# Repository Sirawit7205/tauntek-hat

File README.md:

# Tauntek LogIC Tester Hat

A controller hat for Tauntek LogIC Tester that eliminated a need for external terminal and power source.

The hat features a 3.5" TFT Display, a rotary encoder, and a USB PD circuit to provide tester with 9V directly from USB Type-C.

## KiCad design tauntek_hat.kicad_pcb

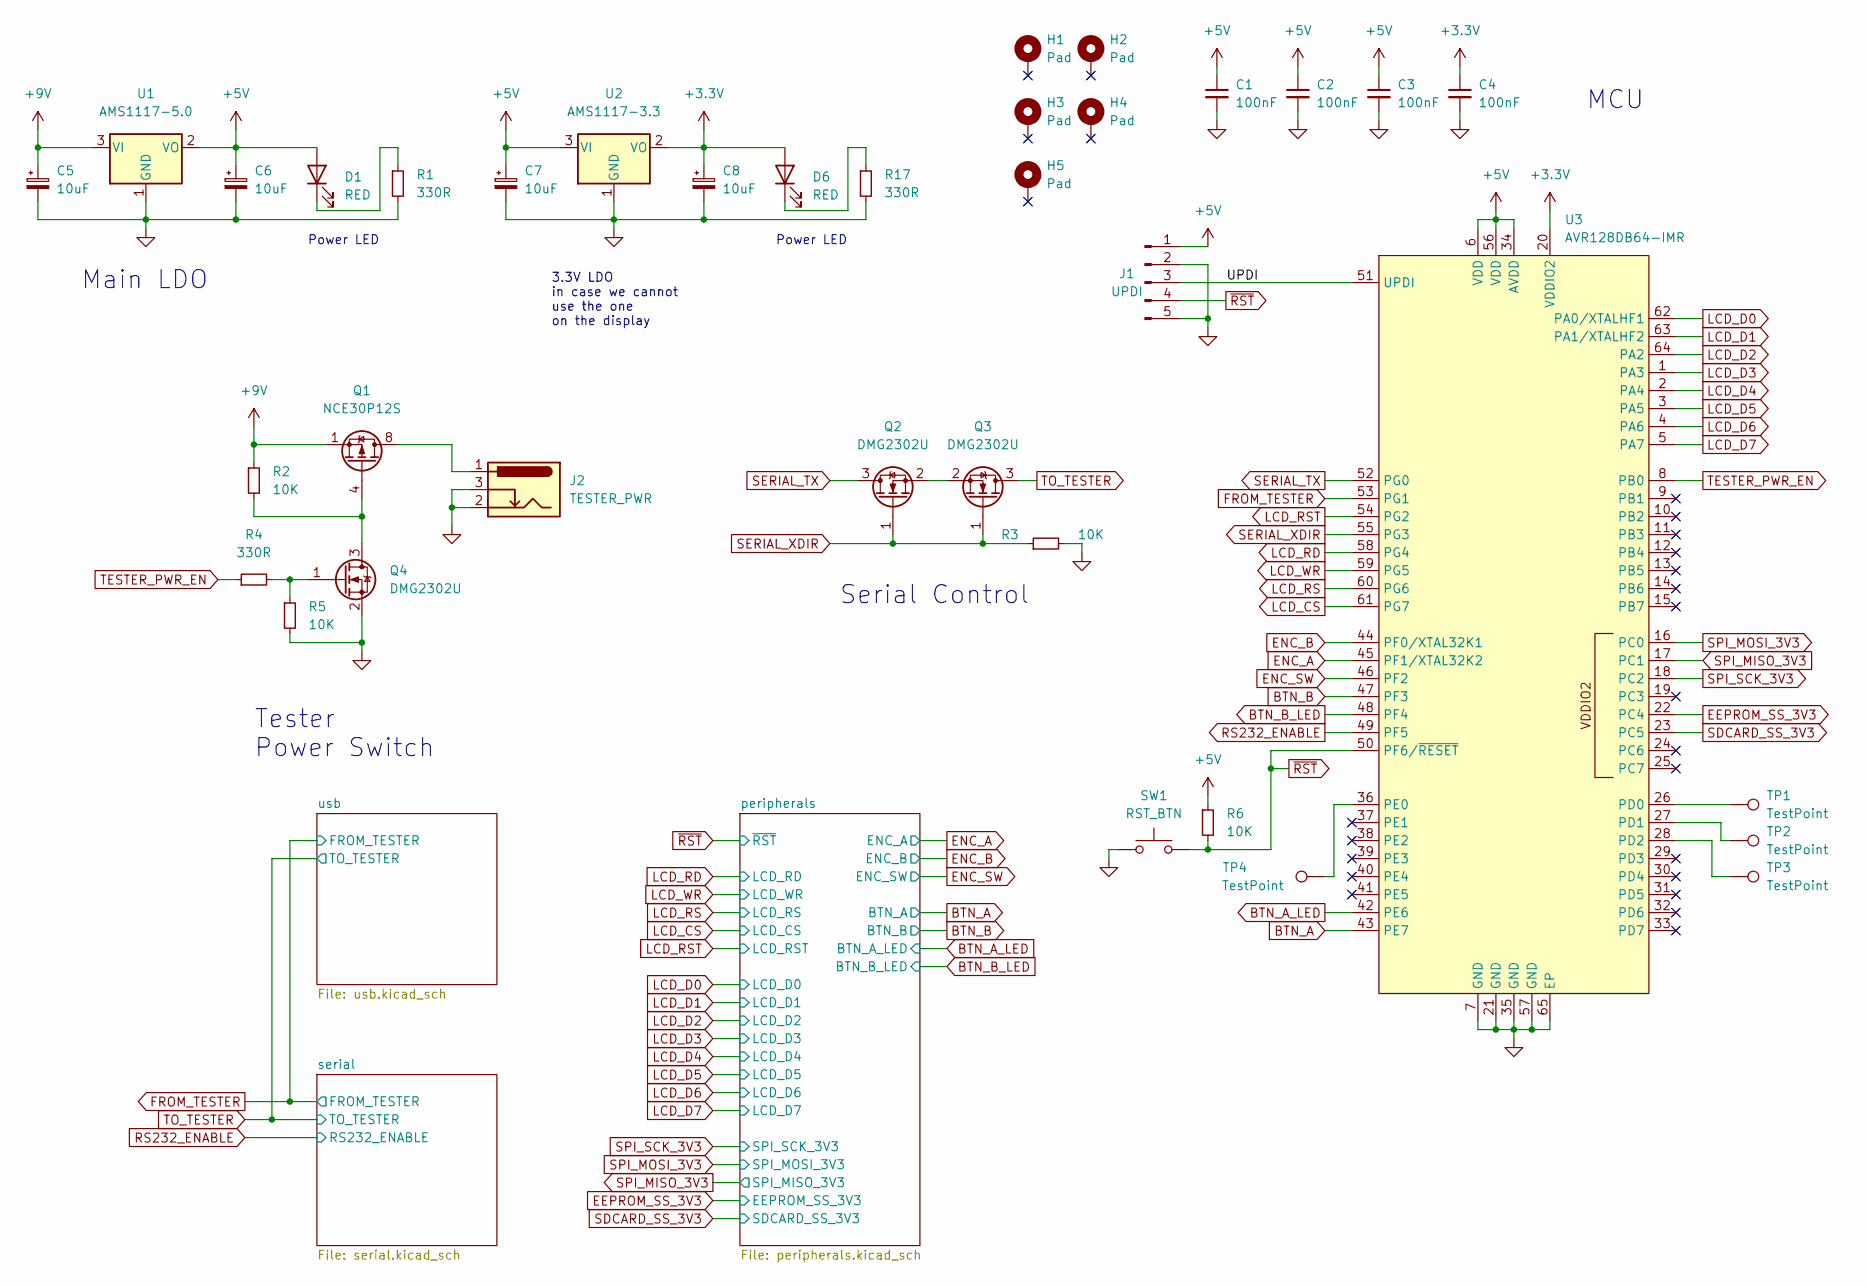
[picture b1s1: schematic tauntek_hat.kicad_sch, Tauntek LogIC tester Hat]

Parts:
C1, C2, C3, C4: 100nF; C_0603_1608Metric
C5, C6, C7, C8: 10uF; CP_Radial_D5.0mm_P2.00mm
D1, D6: RED; LED_D3.0mm
H1, H2, H3, H4, H5: Pad; MountingHole_3mm_Pad
J1: UPDI; PinHeader_1x05_P2.54mm_Vertical
J2: TESTER_PWR
Q1: NCE30P12S; SOIC-8_3.9x4.9mm_P1.27mm
Q2, Q3, Q4: DMG2302U; SOT-23
R1, R4, R17: 330R; R_0603_1608Metric
R2, R3, R5, R6: 10K; R_0603_1608Metric
SW1: RST_BTN; SW_PUSH_6mm
TP1, TP2, TP3, TP4: TestPoint; TestPoint_Pad_D1.0mm
U1: AMS1117-5.0; SOT-223-3_TabPin2
U2: AMS1117-3.3; SOT-223-3_TabPin2
U3: AVR128DB64-IMR

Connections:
+3V3: C4.1, C8.1, D6.2 (A), U2.2 (VO), U3.20 (VDDIO2); also elsewhere on the board
+5V: C1.1, C2.1, C3.1, C6.1, C7.1, D1.2 (A), J1.1, R6.1, U1.2 (VO), U2.3 (VI), U3.6 (VDD), U3.34 (AVDD), U3.56 (VDD); also elsewhere on the board
+9V: C5.1, Q1.1 (S), Q1.2 (S), Q1.3 (S), R2.1, U1.3 (VI); also elsewhere on the board
/UPDI: J1.3, U3.51 (UPDI)
BTN_A: U3.43 (PE7); also elsewhere on the board
BTN_A_LED: U3.42 (PE6); also elsewhere on the board
BTN_B: U3.47 (PF3); also elsewhere on the board
BTN_B_LED: U3.48 (PF4); also elsewhere on the board
EEPROM_SS_3V3: U3.22 (PC4); also elsewhere on the board
ENC_A: U3.45 (PF1/XTAL32K2); also elsewhere on the board
ENC_B: U3.44 (PF0/XTAL32K1); also elsewhere on the board
ENC_SW: U3.46 (PF2); also elsewhere on the board
FROM_TESTER: U3.53 (PG1); also elsewhere on the board
GND: C1.2, C2.2, C3.2, C4.2, C5.2, C6.2, C7.2, C8.2, J1.2, J1.5, J2.2, J2.3, Q4.2 (S), R1.2, R3.2, R5.2, R17.2, SW1.1, U1.1 (GND), U2.1 (GND), U3.7 (GND), U3.21 (GND), U3.35 (GND), U3.57 (GND), U3.65 (EP); also elsewhere on the board
LCD_CS: U3.61 (PG7); also elsewhere on the board
LCD_D0: U3.62 (PA0/XTALHF1); also elsewhere on the board
LCD_D1: U3.63 (PA1/XTALHF2); also elsewhere on the board
LCD_D2: U3.64 (PA2); also elsewhere on the board
LCD_D3: U3.1 (PA3); also elsewhere on the board
LCD_D4: U3.2 (PA4); also elsewhere on the board
LCD_D5: U3.3 (PA5); also elsewhere on the board
LCD_D6: U3.4 (PA6); also elsewhere on the board
LCD_D7: U3.5 (PA7); also elsewhere on the board
LCD_RD: U3.58 (PG4); also elsewhere on the board
LCD_RS: U3.60 (PG6); also elsewhere on the board
LCD_RST: U3.54 (PG2); also elsewhere on the board
LCD_WR: U3.59 (PG5); also elsewhere on the board
unnamed: D1.1 (K), R1.1
unnamed: D6.1 (K), R17.1
unnamed: J2.1, Q1.5 (D), Q1.6 (D), Q1.7 (D), Q1.8 (D)
unnamed: Q1.4 (G), Q4.3 (D), R2.2
unnamed: Q2.2 (S), Q3.2 (S)
unnamed: Q4.1 (G), R4.2, R5.1
unnamed: TP1.1, U3.26 (PD0)
unnamed: TP2.1, U3.27 (PD1)
unnamed: TP3.1, U3.28 (PD2)
unnamed: TP4.1, U3.36 (PE0)
RS232_ENABLE: U3.49 (PF5); also elsewhere on the board
SDCARD_SS_3V3: U3.23 (PC5); also elsewhere on the board
SERIAL_TX: Q2.3 (D), U3.52 (PG0)
SERIAL_XDIR: Q2.1 (G), Q3.1 (G), R3.1, U3.55 (PG3)
SPI_MISO_3V3: U3.17 (PC1); also elsewhere on the board
SPI_MOSI_3V3: U3.16 (PC0); also elsewhere on the board
SPI_SCK_3V3: U3.18 (PC2); also elsewhere on the board
TESTER_PWR_EN: R4.1, U3.8 (PB0)
TO_TESTER: Q3.3 (D); also elsewhere on the board
~RST: J1.4, R6.2, SW1.2, U3.50 (PF6/~RESET); also elsewhere on the board

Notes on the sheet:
Main LDO
3.3V LDO in case we cannot use the one on the display
Tester Power Switch
Serial Control
MCU
Power LED

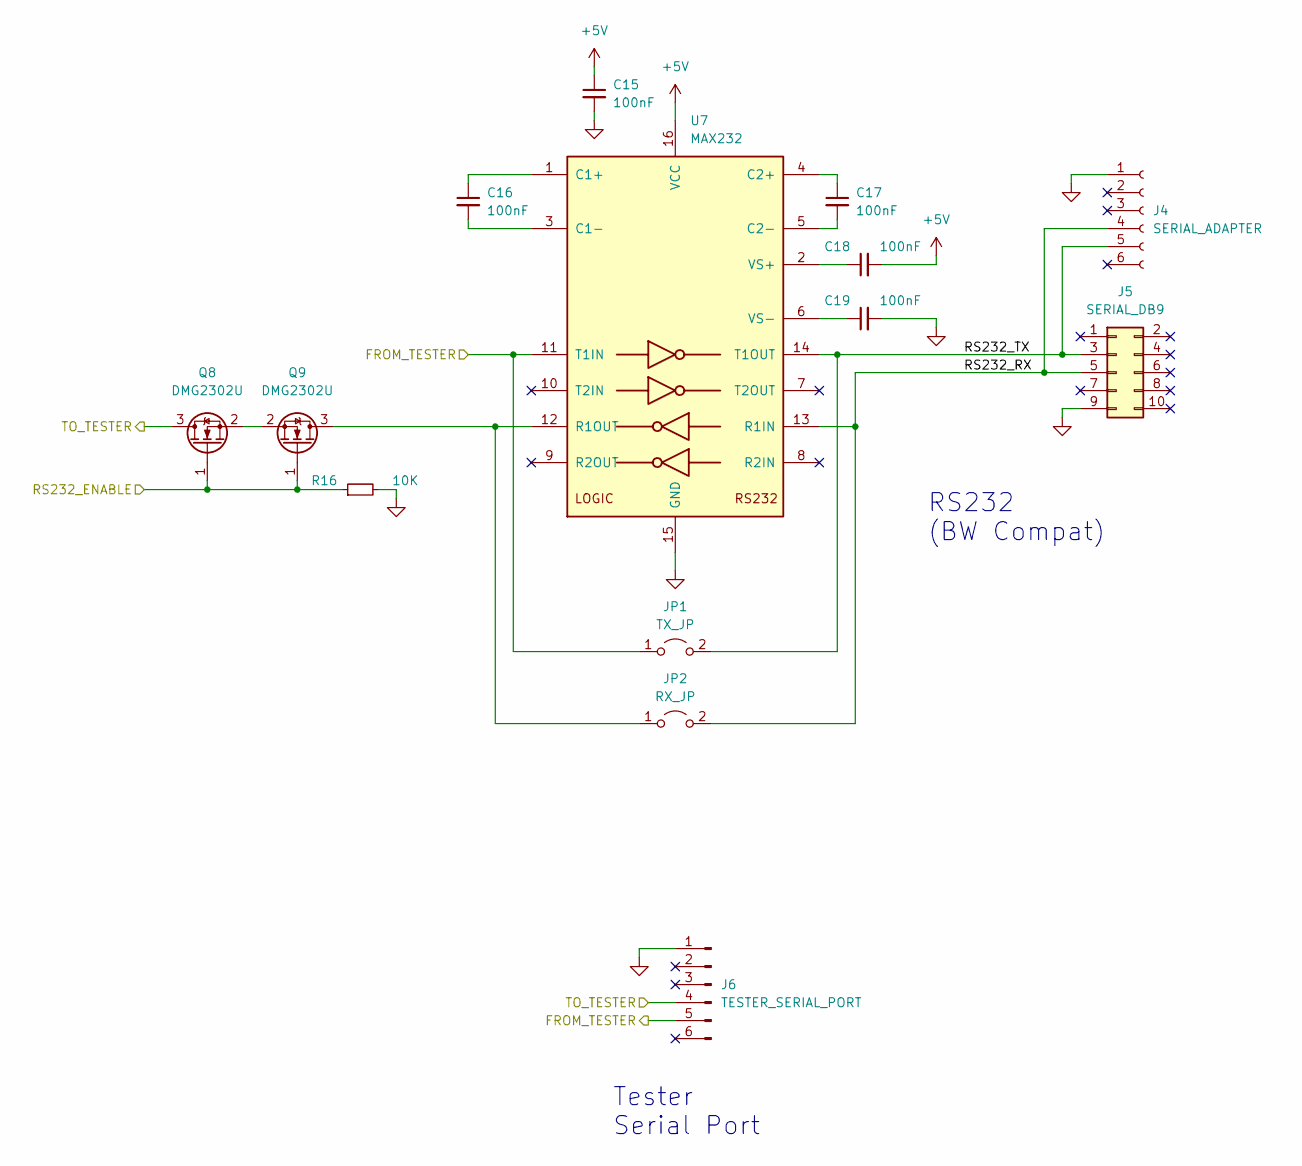
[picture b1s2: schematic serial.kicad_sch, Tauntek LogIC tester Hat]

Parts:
C15, C16, C17, C18, C19: 100nF; C_Rect_L4.6mm_W2.0mm_P2.50mm_MKS02_FKP02
J4: SERIAL_ADAPTER; PinHeader_1x06_P2.54mm_Vertical
J5: SERIAL_DB9; PinHeader_2x05_P2.54mm_Vertical
J6: TESTER_SERIAL_PORT; PinHeader_1x06_P2.54mm_Vertical
JP1: TX_JP; SolderJumper-2_P1.3mm_Open_Pad1.0x1.5mm
JP2: RX_JP; SolderJumper-2_P1.3mm_Open_Pad1.0x1.5mm
Q8, Q9: DMG2302U; SOT-23
R16: 10K; R_0603_1608Metric
U7: MAX232; DIP-16_W7.62mm

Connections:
+5V: C15.1, C18.2, U7.16 (VCC); also elsewhere on the board
/serial/RS232_RX: J4.4, J5.5, JP2.2 (B), U7.13 (R1IN)
/serial/RS232_TX: J4.5, J5.3, JP1.2 (B), U7.14 (T1OUT)
FROM_TESTER: J6.5, JP1.1 (A), U7.11 (T1IN); also elsewhere on the board
GND: C15.2, C19.2, J4.1, J5.9, J6.1, R16.2, U7.15 (GND); also elsewhere on the board
unnamed: C16.1, U7.1 (C1+)
unnamed: C16.2, U7.3 (C1-)
unnamed: C17.1, U7.4 (C2+)
unnamed: C17.2, U7.5 (C2-)
unnamed: C18.1, U7.2 (VS+)
unnamed: C19.1, U7.6 (VS-)
unnamed: JP2.1 (A), Q9.3 (D), U7.12 (R1OUT)
unnamed: Q8.2 (S), Q9.2 (S)
RS232_ENABLE: Q8.1 (G), Q9.1 (G), R16.1; also elsewhere on the board
TO_TESTER: J6.4, Q8.3 (D); also elsewhere on the board

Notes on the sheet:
Tester Serial Port
RS232 (BW Compat)

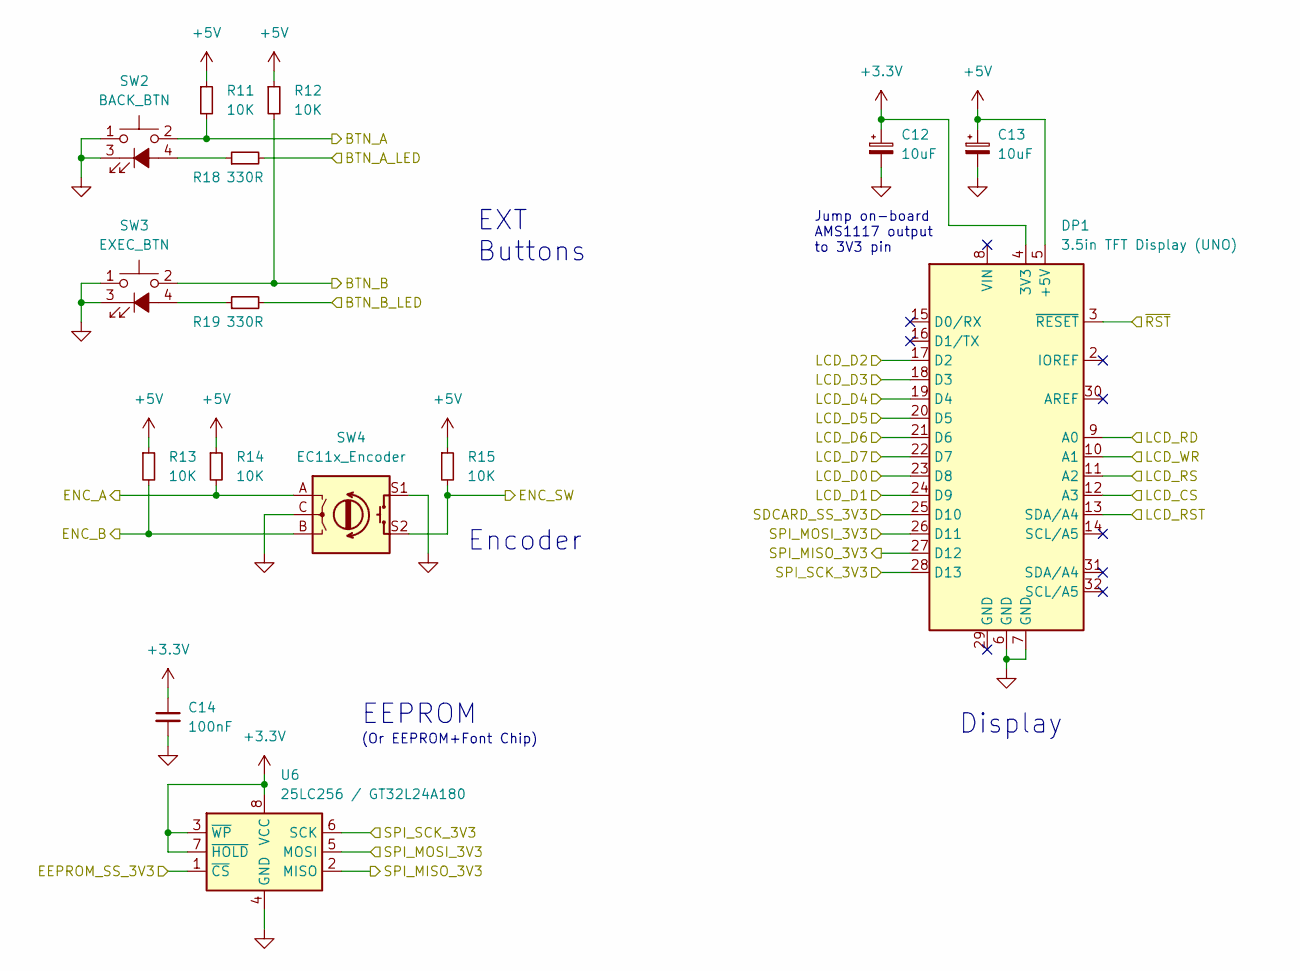
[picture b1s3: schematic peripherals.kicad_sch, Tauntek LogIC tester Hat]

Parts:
C12, C13: 10uF; CP_Radial_D5.0mm_P2.00mm
C14: 100nF; C_0603_1608Metric
DP1: 3.5in TFT Display (UNO); Arduino_UNO_R3_Display
R11, R12, R13, R14, R15: 10K; R_0603_1608Metric
R18, R19: 330R; R_0603_1608Metric
SW2: BACK_BTN; SW_PUSH-12mm_Lamp
SW3: EXEC_BTN; SW_PUSH-12mm_Lamp
SW4: EC11x_Encoder
U6: 25LC256 / GT32L24A180; SOP-8_5.28x5.23mm_P1.27mm_LongPads

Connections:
+3V3: C12.1, C14.1, DP1.4 (3V3), U6.3 (~WP), U6.7 (~HOLD), U6.8 (VCC); also elsewhere on the board
+5V: C13.1, DP1.5 (+5V), R11.1, R12.1, R13.1, R14.1, R15.1; also elsewhere on the board
BTN_A: R11.2, SW2.2; also elsewhere on the board
BTN_A_LED: R18.2; also elsewhere on the board
BTN_B: R12.2, SW3.2; also elsewhere on the board
BTN_B_LED: R19.2; also elsewhere on the board
EEPROM_SS_3V3: U6.1 (~CS); also elsewhere on the board
ENC_A: R14.2, SW4.A; also elsewhere on the board
ENC_B: R13.2, SW4.B; also elsewhere on the board
ENC_SW: R15.2, SW4.S2; also elsewhere on the board
GND: C12.2, C13.2, C14.2, DP1.6 (GND), DP1.7 (GND), SW2.1, SW2.3 (K), SW3.1, SW3.3 (K), SW4.C, SW4.S1, U6.4 (GND); also elsewhere on the board
LCD_CS: DP1.12 (A3); also elsewhere on the board
LCD_D0: DP1.23 (D8); also elsewhere on the board
LCD_D1: DP1.24 (D9); also elsewhere on the board
LCD_D2: DP1.17 (D2); also elsewhere on the board
LCD_D3: DP1.18 (D3); also elsewhere on the board
LCD_D4: DP1.19 (D4); also elsewhere on the board
LCD_D5: DP1.20 (D5); also elsewhere on the board
LCD_D6: DP1.21 (D6); also elsewhere on the board
LCD_D7: DP1.22 (D7); also elsewhere on the board
LCD_RD: DP1.9 (A0); also elsewhere on the board
LCD_RS: DP1.11 (A2); also elsewhere on the board
LCD_RST: DP1.13 (SDA/A4); also elsewhere on the board
LCD_WR: DP1.10 (A1); also elsewhere on the board
unnamed: R18.1, SW2.4 (A)
unnamed: R19.1, SW3.4 (A)
SDCARD_SS_3V3: DP1.25 (D10); also elsewhere on the board
SPI_MISO_3V3: DP1.27 (D12), U6.2 (MISO); also elsewhere on the board
SPI_MOSI_3V3: DP1.26 (D11), U6.5 (MOSI); also elsewhere on the board
SPI_SCK_3V3: DP1.28 (D13), U6.6 (SCK); also elsewhere on the board
~RST: DP1.3 (~RESET); also elsewhere on the board

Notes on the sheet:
Display
(Or EEPROM+Font Chip)
Encoder
EEPROM
EXT Buttons
Jump on-board AMS1117 output to 3V3 pin

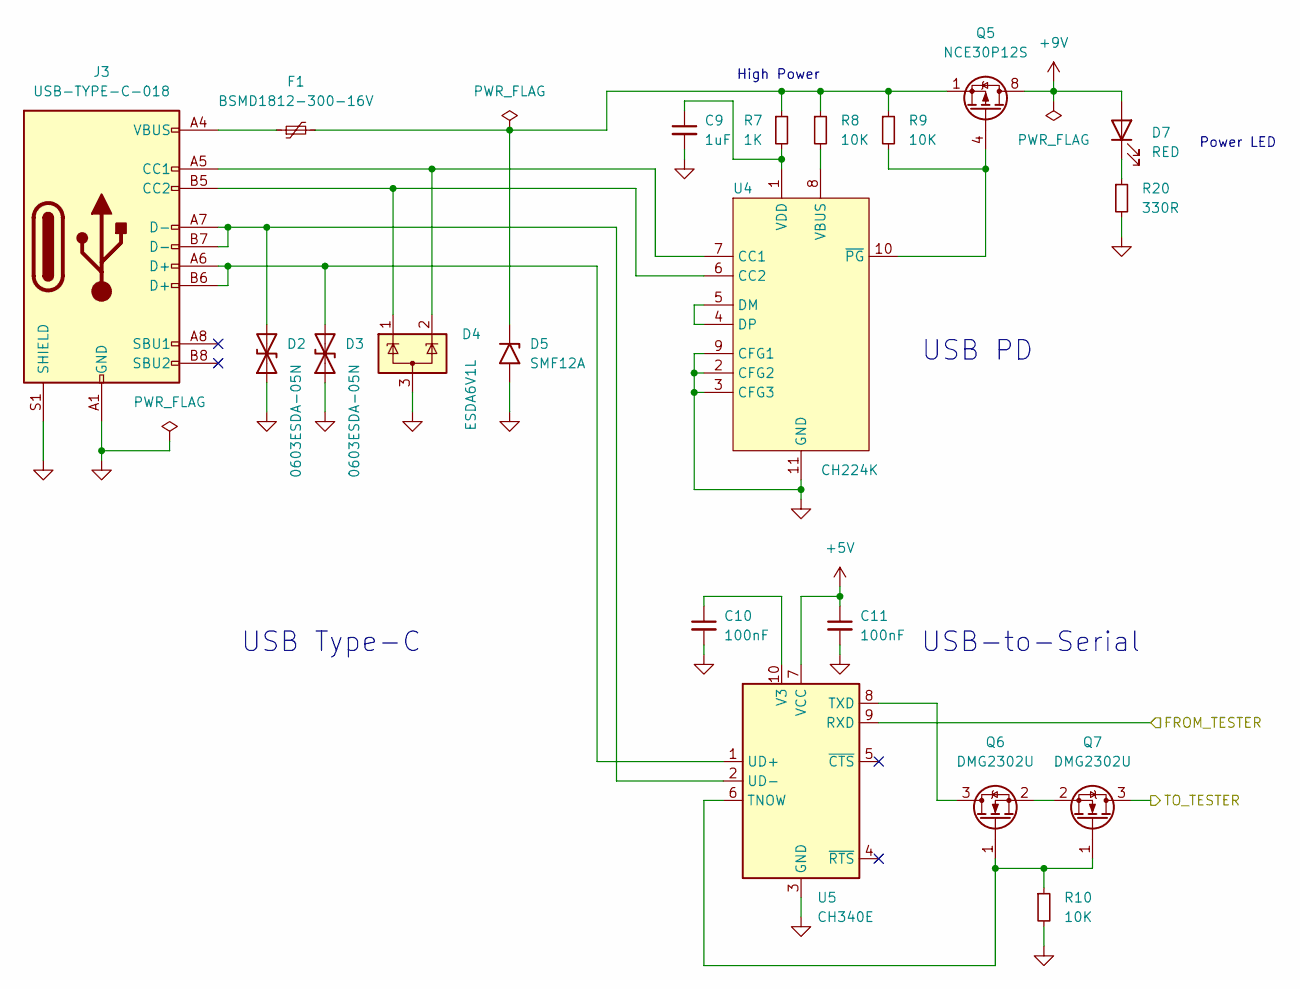
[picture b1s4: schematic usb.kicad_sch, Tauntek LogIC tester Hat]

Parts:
C9: 1uF; C_0603_1608Metric
C10, C11: 100nF; C_0603_1608Metric
D2, D3: 0603ESDA-05N; L_0603_1608Metric
D4: ESDA6V1L; SOT-23
D5: SMF12A; D_SOD-123F
D7: RED; LED_D3.0mm
F1: BSMD1812-300-16V; Fuse_1812_4532Metric
J3: USB-TYPE-C-018
Q5: NCE30P12S; SOIC-8_3.9x4.9mm_P1.27mm
Q6, Q7: DMG2302U; SOT-23
R7: 1K; R_1206_3216Metric
R8, R9, R10: 10K; R_0603_1608Metric
R20: 330R; R_0603_1608Metric
U4: CH224K; ESSOP-10-1EP_3.9x4.9mm_P1.00mm_EP2.29x3mm
U5: CH340E; MSOP-10_3x3mm_P0.5mm

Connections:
+5V: C11.1, U5.7 (VCC); also elsewhere on the board
+9V: D7.2 (A), Q5.5 (D), Q5.6 (D), Q5.7 (D), Q5.8 (D); also elsewhere on the board
FROM_TESTER: U5.9 (RXD); also elsewhere on the board
GND: C9.2, C10.2, C11.2, D2.1 (A1), D3.1 (A1), D4.3 (A), D5.2 (A2), J3.A1 (GND), J3.A12 (GND), J3.B1 (GND), J3.B12 (GND), J3.S1 (SHIELD), R10.2, R20.2, U4.2 (CFG2), U4.3 (CFG3), U4.9 (CFG1), U4.11 (GND), U5.3 (GND); also elsewhere on the board
unnamed: C9.1, R7.2, U4.1 (VDD)
unnamed: C10.1, U5.10 (V3)
unnamed: D2.2 (A2), J3.A7 (D-), J3.B7 (D-), U5.2 (UD-)
unnamed: D3.2 (A2), J3.A6 (D+), J3.B6 (D+), U5.1 (UD+)
unnamed: D4.1 (K), J3.B5 (CC2), U4.6 (CC2)
unnamed: D4.2 (K), J3.A5 (CC1), U4.7 (CC1)
unnamed: D5.1 (A1), F1.2, Q5.1 (S), Q5.2 (S), Q5.3 (S), R7.1, R8.1, R9.1
unnamed: D7.1 (K), R20.1
unnamed: F1.1, J3.A4 (VBUS), J3.A9 (VBUS), J3.B4 (VBUS), J3.B9 (VBUS)
unnamed: Q5.4 (G), R9.2, U4.10 (~PG)
unnamed: Q6.1 (G), Q7.1 (G), R10.1, U5.6 (TNOW)
unnamed: Q6.2 (S), Q7.2 (S)
unnamed: Q6.3 (D), U5.8 (TXD)
unnamed: R8.2, U4.8 (VBUS)
unnamed: U4.4 (DP), U4.5 (DM)
TO_TESTER: Q7.3 (D); also elsewhere on the board

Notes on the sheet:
USB-to-Serial
High Power
USB PD
Power LED
USB Type-C

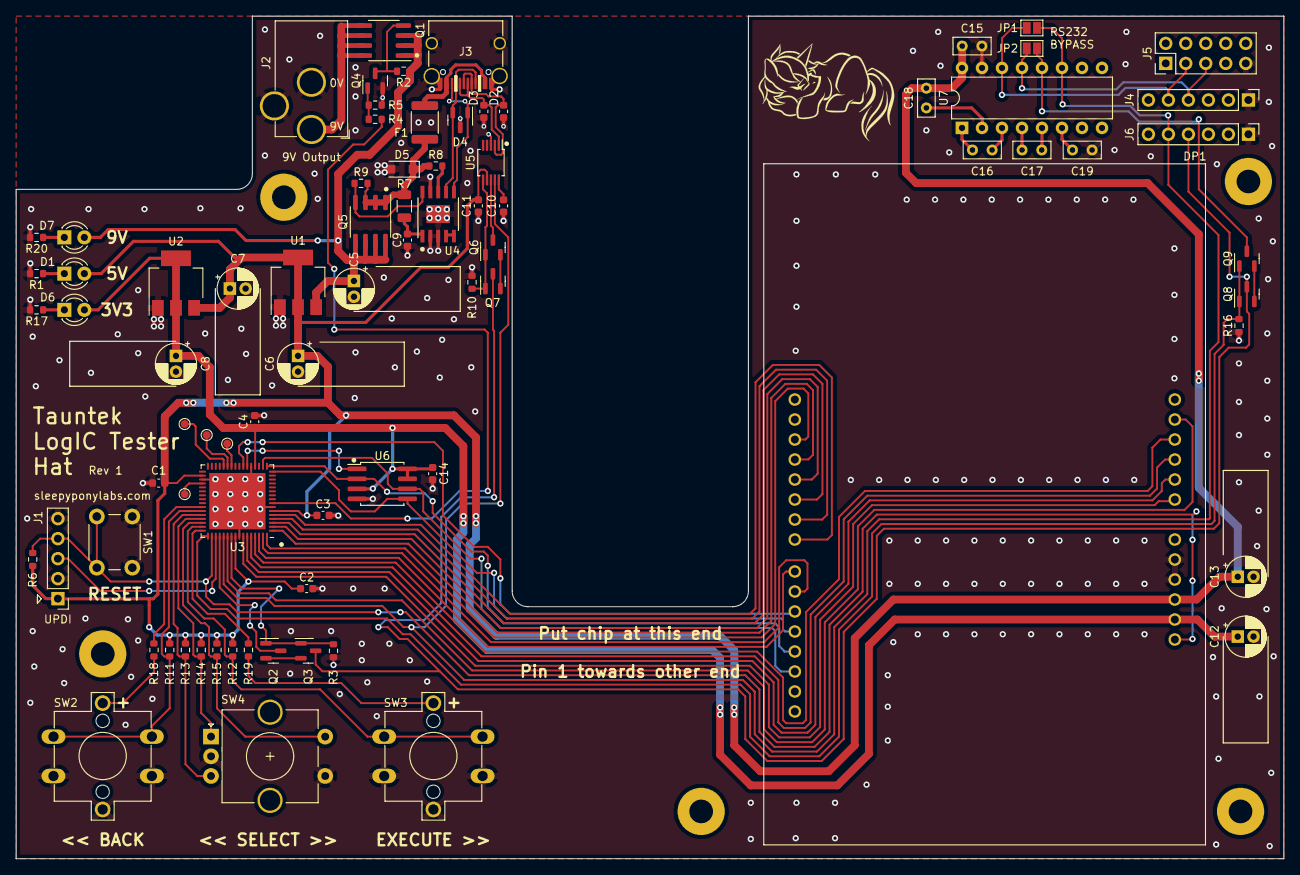
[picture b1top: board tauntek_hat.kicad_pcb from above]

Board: 2 copper layers, 161.0 x 107.0 mm, 85 parts (0 on the bottom side), 74 nets.

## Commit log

2022-06-20 Modified PCB for Aisler budget tier
